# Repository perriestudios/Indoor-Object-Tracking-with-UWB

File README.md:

# <p align="center">Indoor-Object-Tracking-using-UWB </p>
## Introduction

<p align= "justify" > The objective of this project was to create an accurate general-purpose indoor localization system. Ultra-wideband(UWB) a wireless radio technology was chosen to achieve this. UWB offers high accuracy of localization, low latency, minimal interference and noise, and large bandwidth. DW1000 is an RF TX/RX IC manufactured by Decawave for UWB applications. This project uses the DW1000 IC in the form factor of module DWM1000. The hardware for the project was designed around this module with a few preferable features like access to the internet using an ESP8266-12E and programming support using the Arduino IDE. The system uses the Two-Way Ranging(TWR) technique for localization. The position computing is done by trilateration on the tag which is coupled with the object being tracked. A localization accuracy of about 12cm was achieved in a room of size 3x3m.</p>

## System Design

<p align= "justify" > In order to track an object, a device addressed "Tag" is attached to it. Devices callled "Anchors" are placed around the indoor environment to provide a spatial reference for the tag. Before the system starts tracking, the anchors should be fixed at different locations in the room and their coordinates are programmed in the tag. As shown in the above block diagram, the anchors are placed at (x1,y1),(x2,y2) and (x3,y3) respectively. Calibration of the DWM1000 is then done to accomodate for the slight difference in the radiation pattern of each antenna as mentioned in the datasheet of the module.</p>

## Working

<p align= "justify" > Once the setup is ready, the tag performs Two-Way Ranging to determine its distance from each anchor. The three distances are then substituted into the trilateration formula to determine the exact position. This data may then be shared with an anchor with a Wi-Fi module called the master anchor. The master anchor can then update the data anywhere over the internet. In this project, a dynamic webpage hosted on the ESP8266 displays the coordinates of the object. This entire cycle is repeated to track the position of the tag(in turn the object) in real time. A flow chart of the process is shown below:</p>

## Hardware
### PCB: Version 1

<p align= "justify" > As stated in the introduction, the hardware was designed around the DWM1000 module. Since the module operates between 2.8-3.6v, the system voltage was fixed to be 3v3. This also provided the convinience of using a handy single cell 750mah lipo battery. ATmega328P was chosen as the microcontroller due to my familiarity with it. An external 8MHz crystal oscillator was connected to ensure the microcontroller is clocked at the fastest possible speed at 3v3. The minimal circuit required for ESP8266 was designed and interfaced with the ATmega328P over the I2C bus while the DWM1000 uses SPI. IC MIC5219 a low cost 500mA LDO was used to regulate the supply voltage to 3v3 from the battery. Additionally, reverse polarity protection using a diode is added. Switches were provided to control power and reset of ATmega328P and ESP8266, while LED's were provided to indicate the status of power and DWM1000.</p>

<p align= "justify" > The above PCB was designed in Autodesk Eagle. The design files can be found in the folder Master_V1 under the Hardware section of this repository. </p>

### PCB: Version 2

<p align= "justify" > The major feature of version 2 addition of programming over the USB. In the previous version, the bootloader was initally burned using an ATMEL ICE debugger and the program written over UART using an Arduino Uno performing USB-TTL conversion. However, I found it very inconvienient to interconnect the Uno everytime, reset it during programming and reading the data serially. Hence, the popular USB-TTL converter CH340G was added to support quicker programming and access to serial monitor. Pads were placed on the bottom to burn the bootloader using pogo pins. I also reduced the size of the crystals and switches to achieve the smallest possible form factor. </p>

<p align= "justify" > The design files can be found under the Tag_V2 and Anchor_V2 folders respectively. The anchor design contains an additional ESP8266 placed in the bottom. </p>

### Enclosure

<p align= "justify" > An enclosure was designed to house the device in Autodesk Fusion 360. The base was intended to be 3d printed on a PLA base which the lid will be a transparent laser cut acrylic. The PCB will be screwed on to the enclosure. The design file can be found under the hardware section</p>

## Software

<p align= "justify" > The firmware for the project was completely written in Arduino IDE with <a href="https://github.com/thotro/arduino-dw1000" target="_blank" rel="noopener noreferrer">arduino-dw1000 library</a> developed by Thomas Trojer. The programs could be found under the software section of this repository. </p>

## Working

<p align= "justify" > After uploading the program, the tag should be set in calibration mode to perform TWR and correct the calibration constant. After this, open a browser and navigate to the IP addess mentioned in the serial monitor of the master-anchor. The position of the tag will be updated every 10s in real-time with an accuracy < 30cm.</p>

## Outcome

<p align= "justify" >This capstone project was undertaken as part of my UG curriculum. Version 2 of the hardware did not progress beyond the design stage due to my graduation in May 2020, during the middle of the pandemic here. Fortunately, I was able to demonstate the working of the system using the first version of the hardware to earn my degree. However, as a hobby project, I am working on a TDoA implementation of the system to be deployed at Beeclust MRSL for tracking robots. It will be replacement for the april tags currently used in the projects. There are certain aspects of the system that could still be improved. Feel free to contact me if you would like to improve this project.</p>

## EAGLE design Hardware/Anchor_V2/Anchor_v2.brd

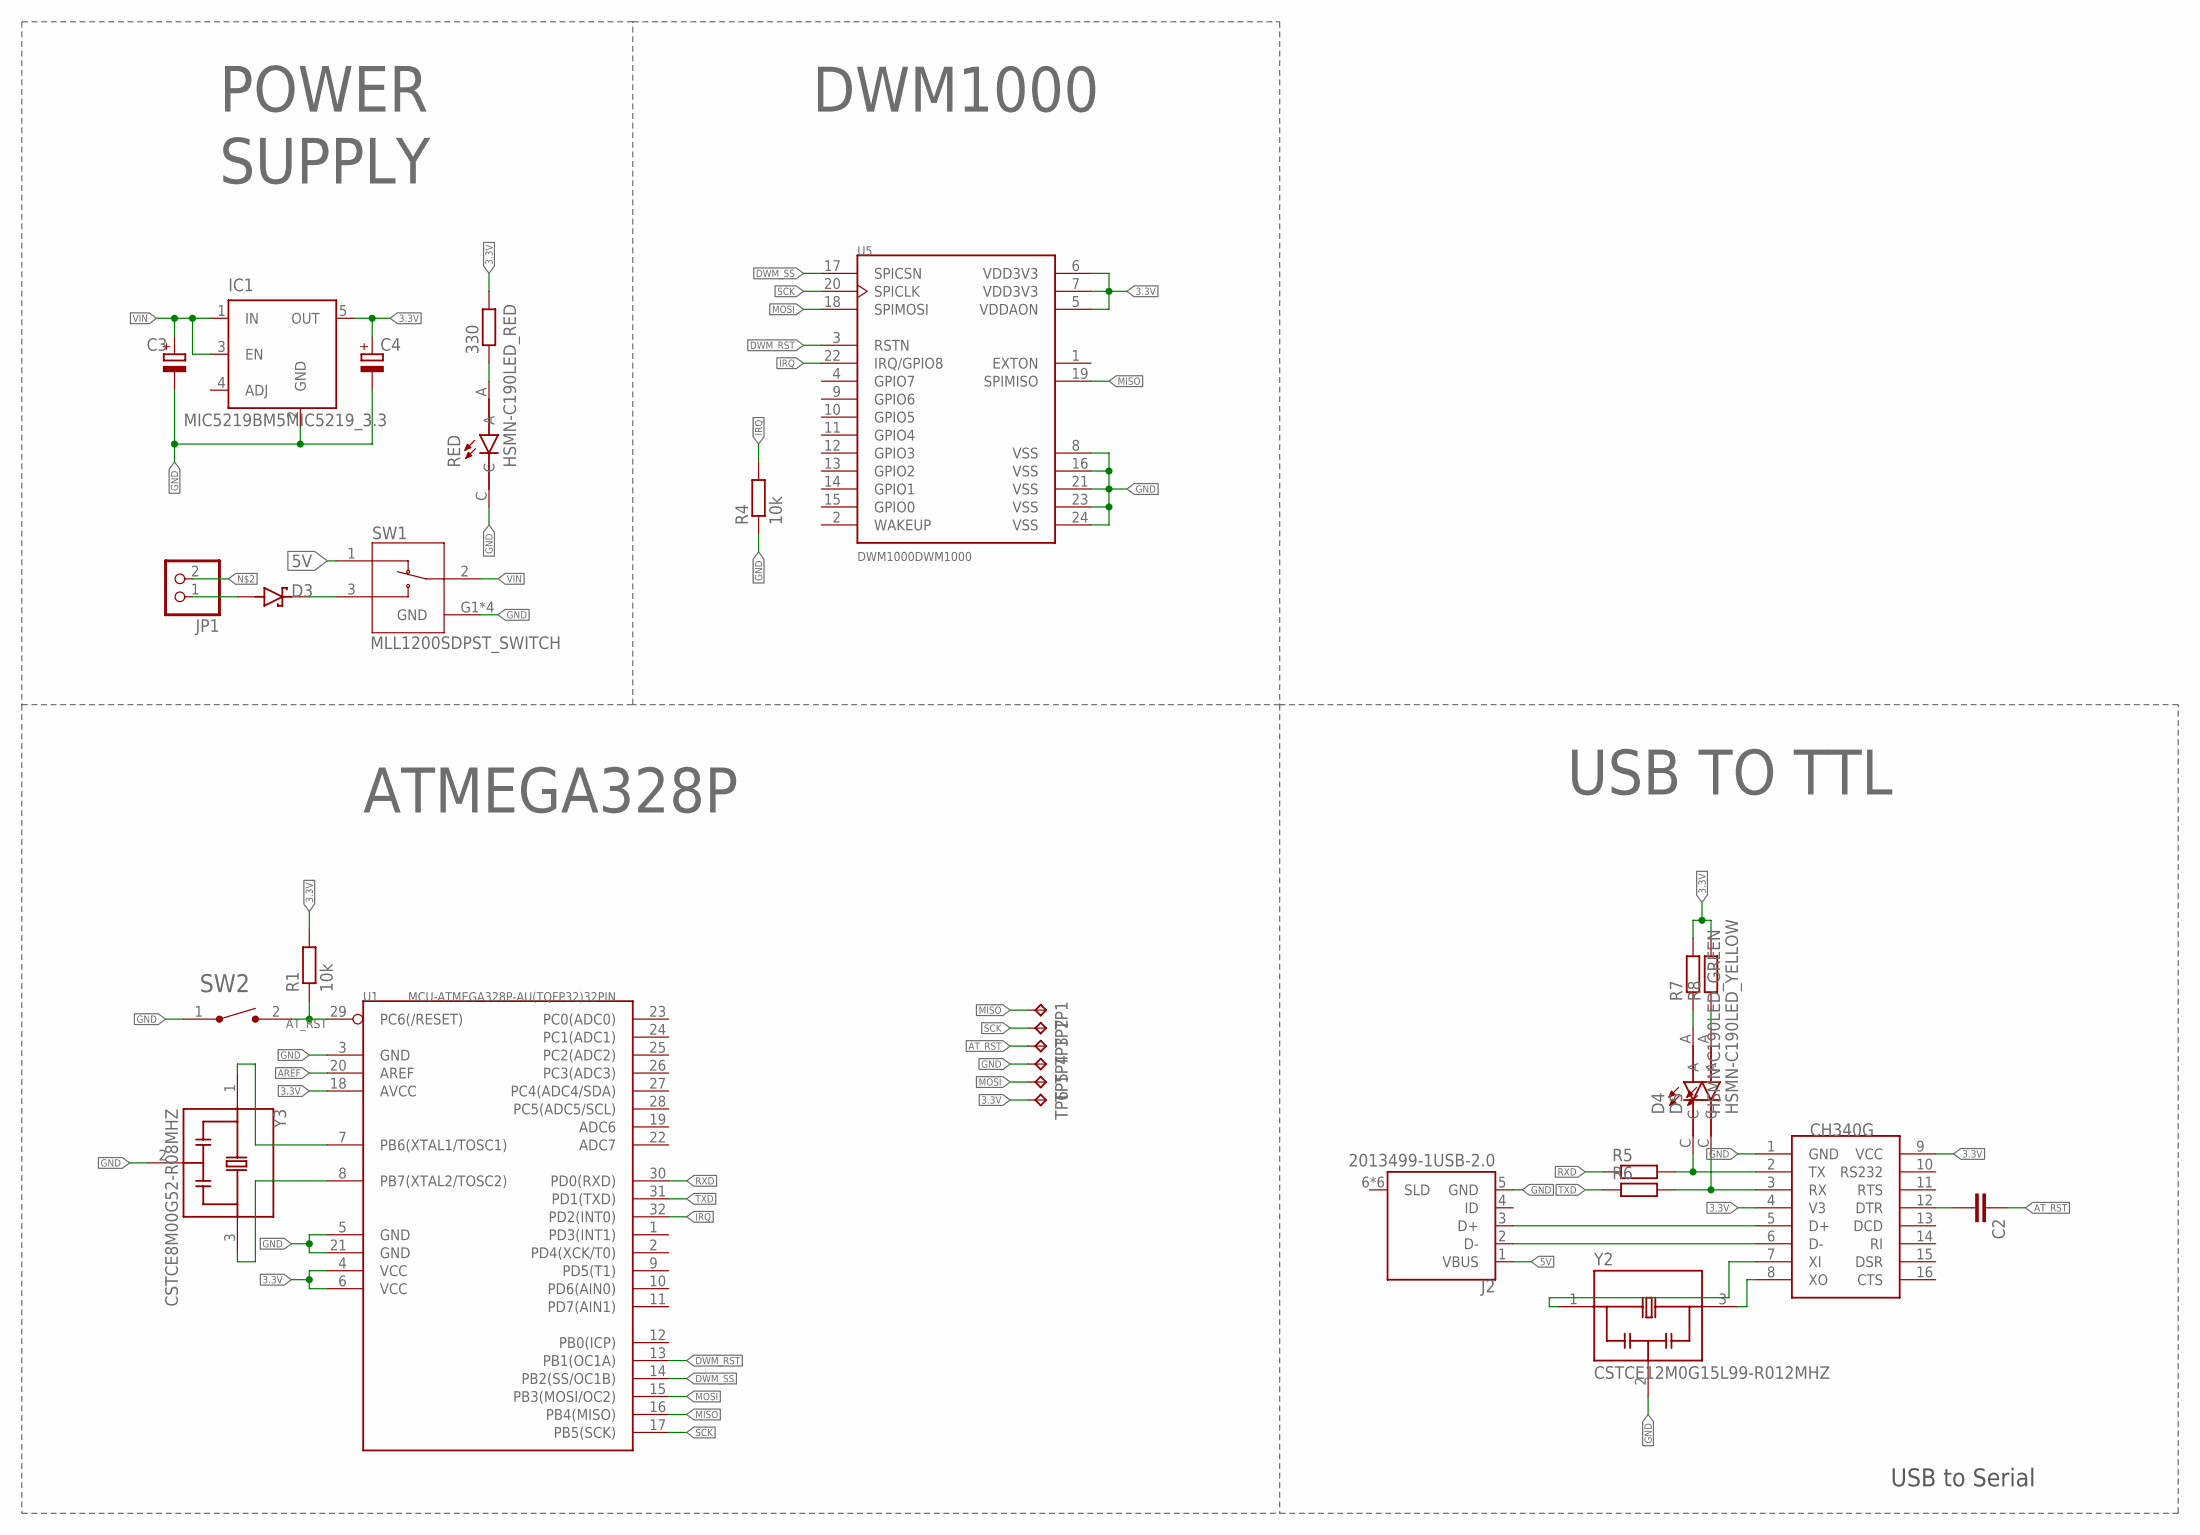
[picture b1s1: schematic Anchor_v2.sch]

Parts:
330: R-EU_R0603; R0603
C2: C-EUC0603; C0603
C3, C4: CPOL-EUA/3216-18R; A/3216-18R
D3: 1N5819HW-7-FSCHOTTKEYDIODE; SOD3715X145N_NEW
D4: HSMN-C190LED_GREEN; LEDM1608X80_NEW
D5: HSMN-C190LED_YELLOW; LEDM1608X80_NEW
IC1: MIC5219BM5MIC5219_3.3; SOT23-5_NEW
J2: 2013499-1USB-2.0; TE_2013499-1_NEW
JP1: PINHD-1X2; 1X02
R1, R4: 10k; R0603
R5, R6, R7, R8: R-EU_R0603; R0603
RED: HSMN-C190LED_RED; LEDM1608X80_NEW
SW1: MLL1200SDPST_SWITCH; SW_MLL1200S_NEW
SW2: FSMSMRESET_SPST; TE_FSMSM_NEW
TP1, TP2, TP3, TP4, TP5, TP6: TPB1,27; B1,27
U1: MCU-ATMEGA328P-AU(TQFP32)32PIN; TQFP32-0.8-7X7MM_NEW
U5: DWM1000DWM1000; XCVR_DWM1000_NEW
U$1: CH340G16PIN; SOIC16_NEW
Y2: CSTCE12M0G15L99-R012MHZ; OSC_CSTCE12M0G15L99-R0_NEW
Y3: CSTCE8M00G52-R08MHZ; OSC_CSTCE8M00G52-R0_NEW

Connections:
3.3V: 330.2, C4.+, IC1.5 (OUT), R1.2, R7.2, R8.2, TP6.TP, U1.4 (VCC), U1.6 (VCC), U1.18 (AVCC), U5.5 (VDDAON), U5.6 (VDD3V3), U5.7 (VDD3V3), U$1.4 (V3), U$1.9 (VCC)
5V: J2.1 (VBUS), SW1.1
AREF: U1.20 (AREF)
AT_RST: C2.1, R1.1, SW2.2, TP3.TP, U1.29 (PC6(/RESET))
DWM_RST: U1.13 (PB1(OC1A)), U5.3 (RSTN)
DWM_SS: U1.14 (PB2(SS/OC1B)), U5.17 (SPICSN)
GND: C3.-, C4.-, IC1.2 (GND), J2.5 (GND), R4.1, RED.C, SW1.G1 (GND), SW1.G2 (GND), SW1.G3 (GND), SW1.G4 (GND), SW2.1, TP4.TP, U1.3 (GND), U1.5 (GND), U1.21 (GND), U5.8 (VSS), U5.16 (VSS), U5.21 (VSS), U5.23 (VSS), U5.24 (VSS), U$1.1 (GND), Y2.2, Y3.2
IRQ: R4.2, U1.32 (PD2(INT0)), U5.22 (IRQ/GPIO8)
MISO: TP1.TP, U1.16 (PB4(MISO)), U5.19 (SPIMISO)
MOSI: TP5.TP, U1.15 (PB3(MOSI/OC2)), U5.18 (SPIMOSI)
unnamed: U1.7 (PB6(XTAL1/TOSC1)), Y3.1
unnamed: D3.A, JP1.1
unnamed: D3.C (K), SW1.3
unnamed: U1.8 (PB7(XTAL2/TOSC2)), Y3.3
unnamed: 330.1, RED.A
unnamed: D4.C, R5.2, U$1.2 (TX)
unnamed: C2.2, U$1.12 (DTR)
unnamed: U$1.8 (XO), Y2.3
unnamed: D5.C, R6.2, U$1.3 (RX)
unnamed: D4.A, R7.1
unnamed: D5.A, R8.1
unnamed: U$1.7 (XI), Y2.1
unnamed: J2.2 (D-), U$1.6 (D-)
unnamed: J2.3 (D+), U$1.5 (D+)
RXD: R5.1, U1.30 (PD0(RXD))
SCK: TP2.TP, U1.17 (PB5(SCK)), U5.20 (SPICLK)
TXD: R6.1, U1.31 (PD1(TXD))
VIN: C3.+, IC1.1 (IN), IC1.3 (EN), SW1.2

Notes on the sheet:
POWER
SUPPLY
USB to Serial
DWM1000
ATMEGA328P
USB TO TTL

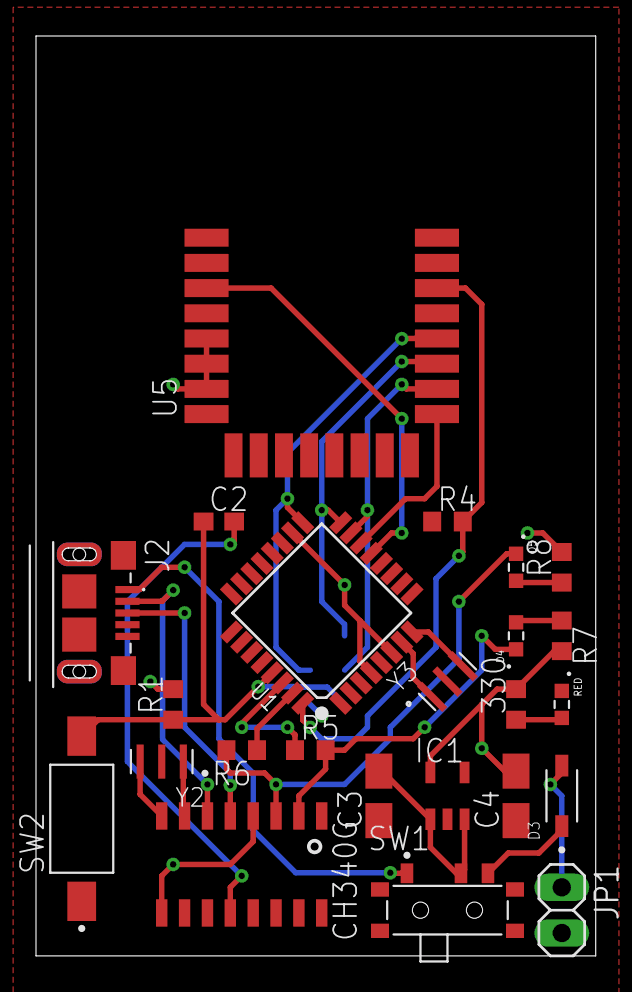
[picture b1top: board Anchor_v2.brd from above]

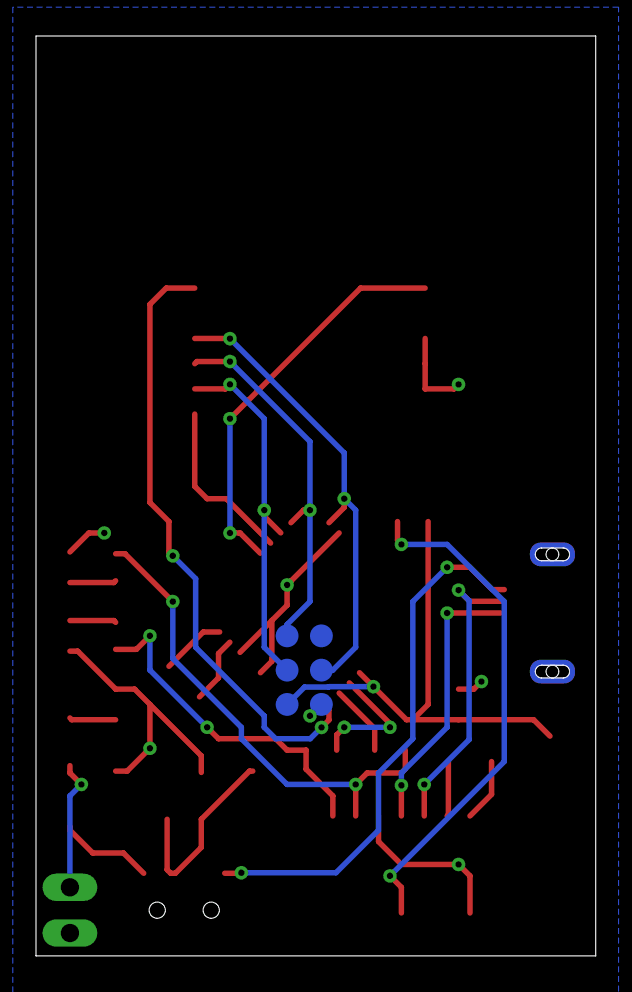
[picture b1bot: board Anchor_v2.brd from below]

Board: 2 copper layers, 31.1 x 51.1 mm, 30 parts (6 on the bottom side), 27 nets.

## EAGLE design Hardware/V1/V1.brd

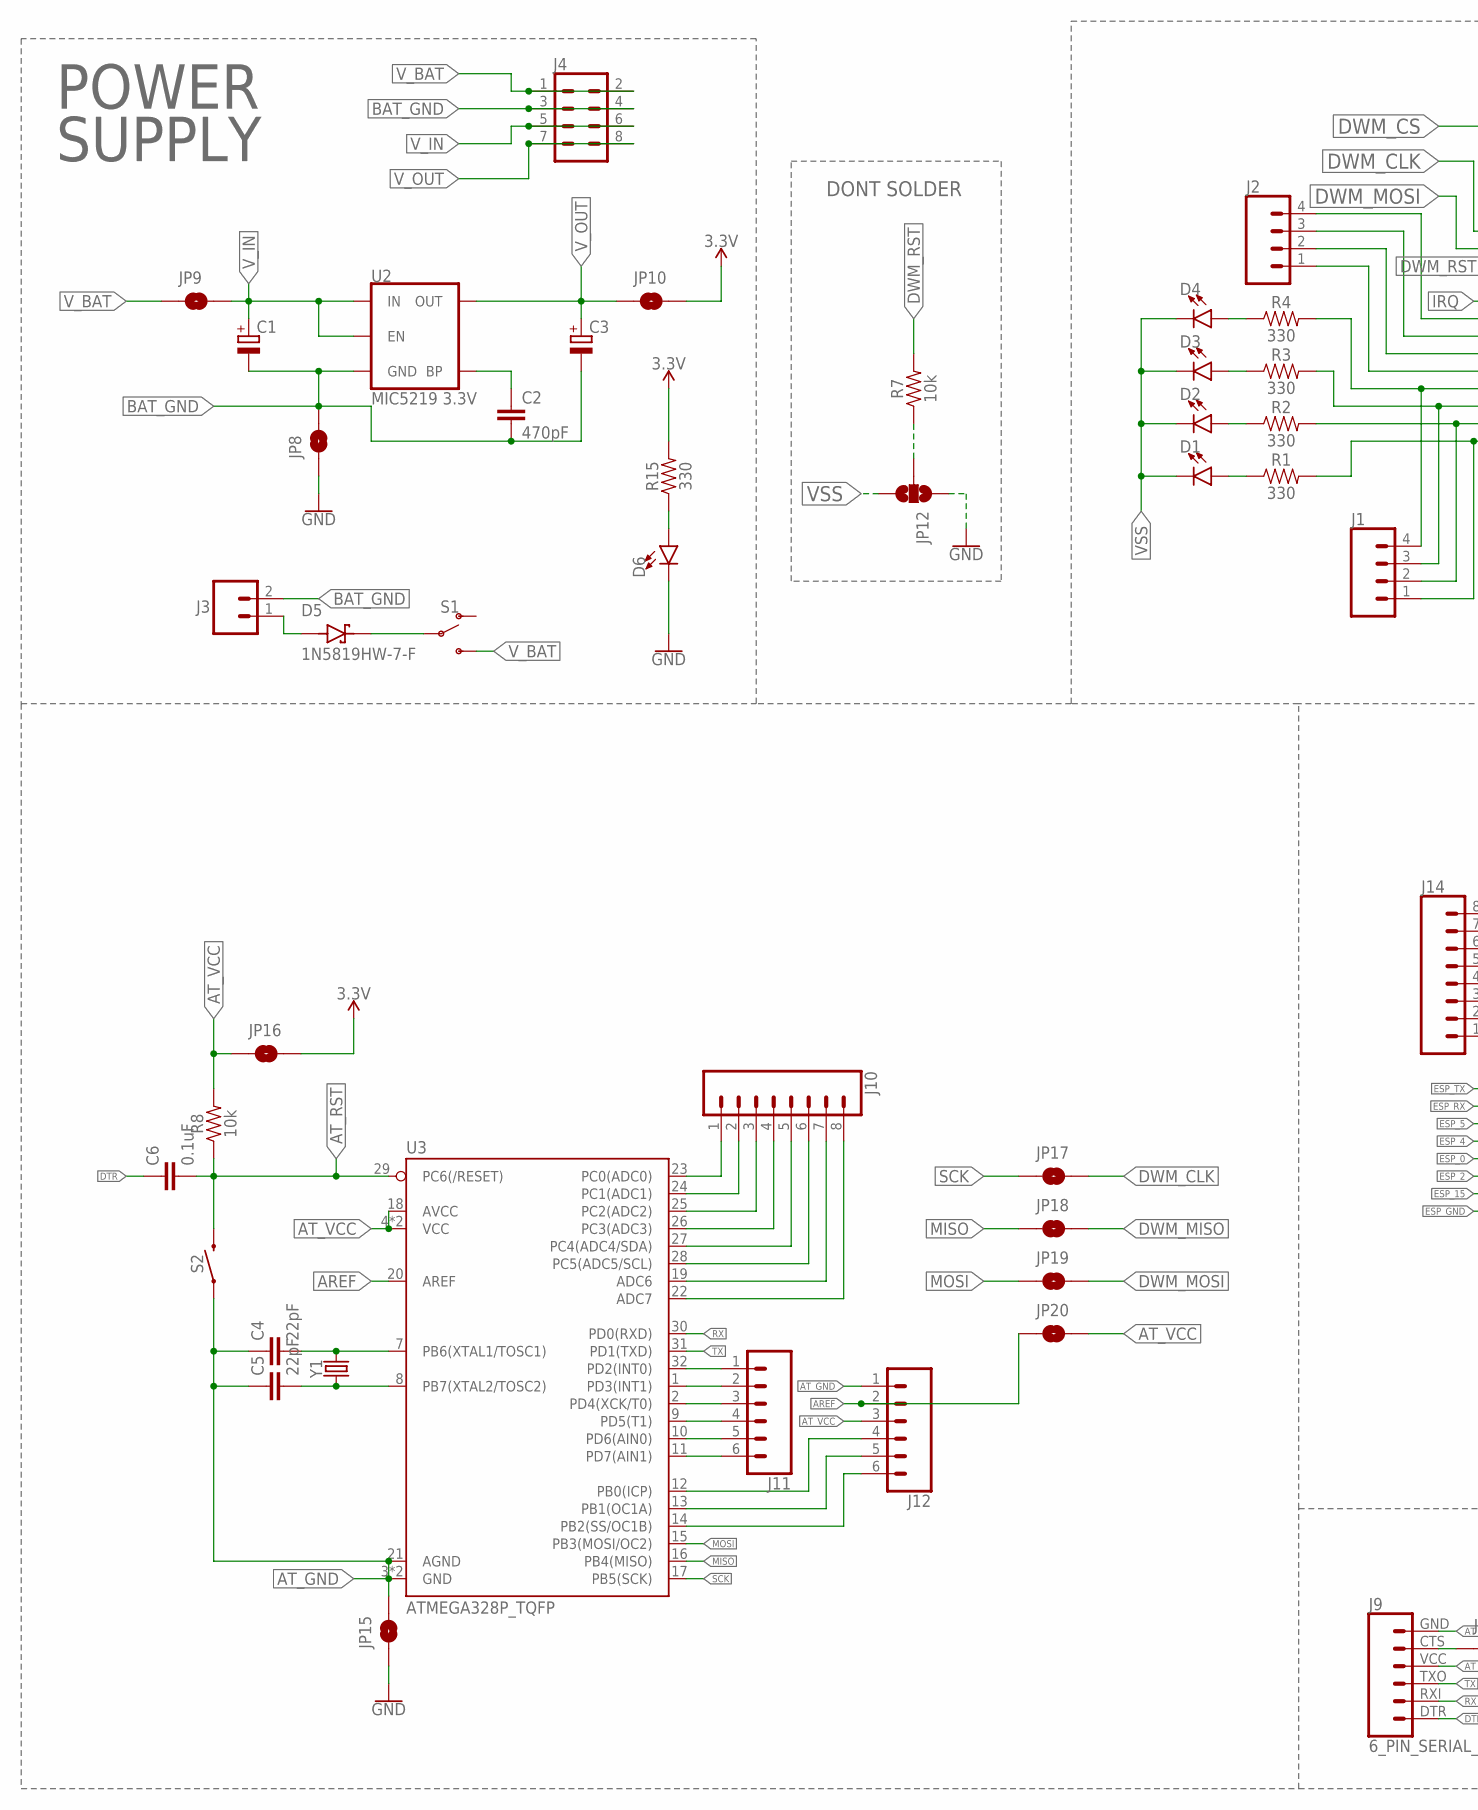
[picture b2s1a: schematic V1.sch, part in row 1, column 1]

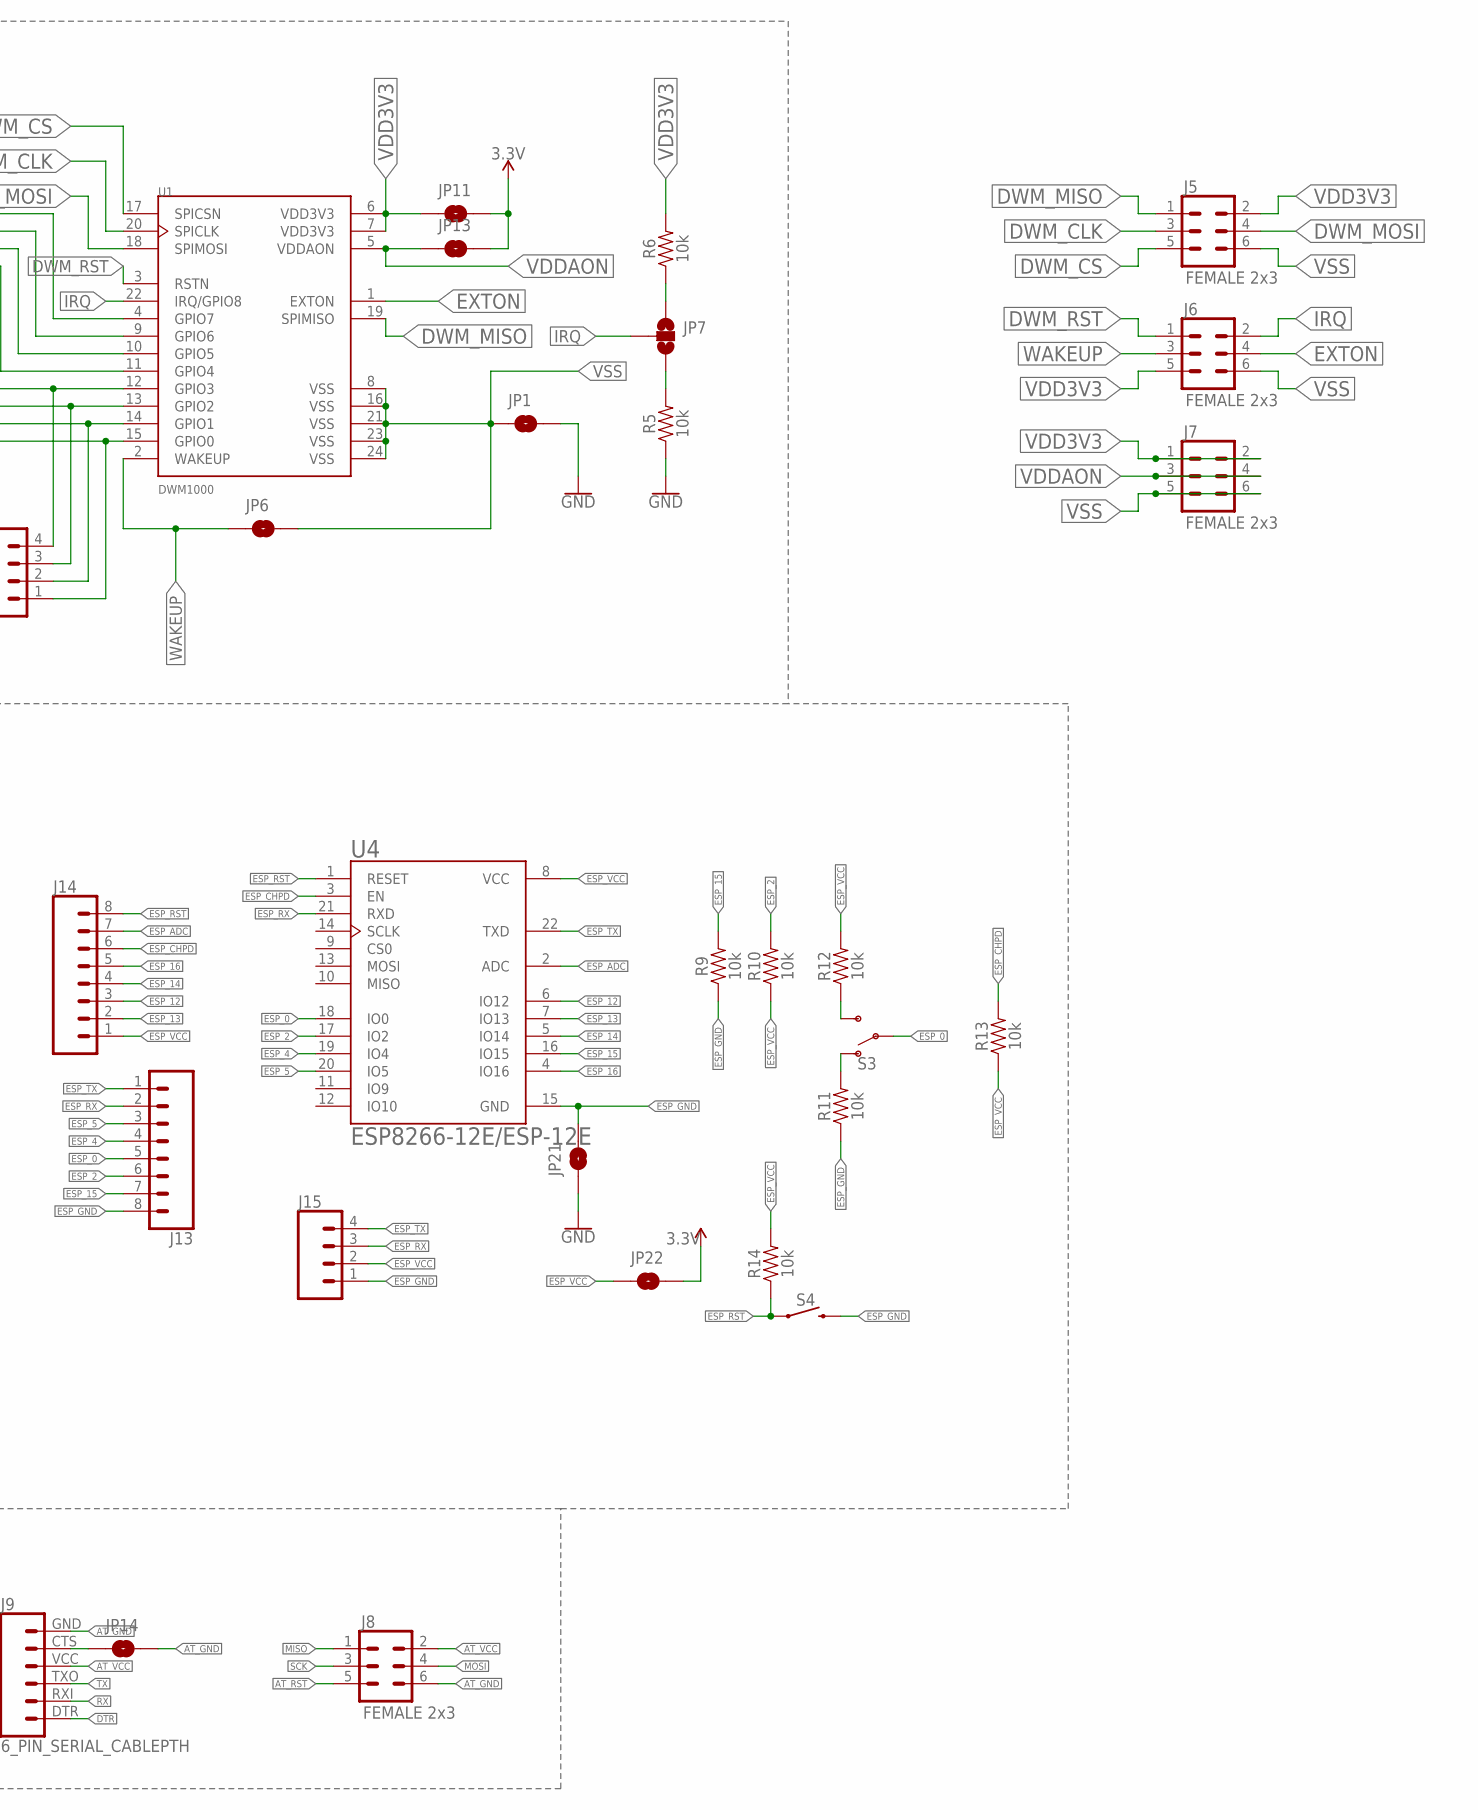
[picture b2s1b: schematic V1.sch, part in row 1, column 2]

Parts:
C1, C3: CPOL-EUSMCA; SMC_A
C2: 470pF; 0603
C4, C5: 22pF; 0603
C6: 0.1uF; 0603
D1, D2, D3, D4, D6: LED0603; LED-0603
D5: 1N5819HW-7-F; SOD3715X145N
J1, J2, J15: CONN_04; 1X04
J3: CONN_02; 1X02
J4: CONN_04X2; 2X4
J5, J6, J7, J8: FEMALE 2x3; 2X3
J9: 6_PIN_SERIAL_CABLEPTH; FTDI_BASIC
J10, J13, J14: CONN_08"; 1X08
J11, J12: CONN_06SILK_FEMALE_PTH; 1X06
JP1, JP6, JP8, JP9, JP10, JP11, JP13, JP14, JP15, JP16, JP17, JP18, JP19, JP20, JP21, JP22: JUMPER-SMT_2_NO_NO-SILK; SMT-JUMPER_2_NO_NO-SILK
JP7, JP12: JUMPER-SMT_3_NO_NO_SILK; SMT-JUMPER_3_0-NO_TRACE_NO-SILK
R1, R2, R3, R4, R15: 330; 0603
R5, R6, R7, R8, R9, R10, R11, R12, R13, R14: 10k; 0603
S1, S3: SWITCH-SPDT-SMD-AYZ0202; SWITCH_DPDT_SMD_AYZ0202
S2, S4: MOMENTARY-SWITCH-SPST-SMD-6.0X3.5MM; TACTILE_SWITCH_SMD_6.0X3.5MM
U1: DWM1000; XCVR_DWM1000
U2: MIC5219 3.3V; SOT23-5
U3: ATMEGA328P_TQFP; TQFP32-08
U4: ESP8266-12E/ESP-12E; XCVR_ESP8266-12E/ESP-12E
Y1: CRYSTALSMD-HC49UP; HC49UP

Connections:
3.3V: JP10.2, JP11.2, JP13.2, JP16.2, JP22.2, R15.2
AREF: J12.2, JP20.1, U3.20 (AREF)
AT_GND: C4.1, C5.1, J8.6, J9.GND (6), J12.1, JP14.2, JP15.2, S2.1, U3.3 (GND), U3.5 (GND), U3.21 (AGND)
AT_RST: C6.2, J8.5, R8.1, S2.2, U3.29 (PC6(/RESET))
AT_VCC: J8.2, J9.VCC (4), J12.3, JP16.1, JP20.2, R8.2, U3.4 (VCC), U3.6 (VCC), U3.18 (AVCC)
BAT_GND: C1.-, C2.2, C3.-, J3.2, J4.3, J4.4, JP8.2, U2.2 (GND)
DTR: C6.1, J9.DTR (1)
DWM_CLK: J5.3, JP17.2, U1.20 (SPICLK)
DWM_CS: J5.5, U1.17 (SPICSN)
DWM_MISO: J5.1, JP18.2, U1.19 (SPIMISO)
DWM_MOSI: J5.4, JP19.2, U1.18 (SPIMOSI)
DWM_RST: J6.1, R7.2, U1.3 (RSTN)
ESP_0: J13.5, S3.2, U4.18 (IO0)
ESP_2: J13.6, R10.2, U4.17 (IO2)
ESP_4: J13.4, U4.19 (IO4)
ESP_5: J13.3, U4.20 (IO5)
ESP_12: J14.3, U4.6 (IO12)
ESP_13: J14.2, U4.7 (IO13)
ESP_14: J14.4, U4.5 (IO14)
ESP_15: J13.7, R9.2, U4.16 (IO15)
ESP_16: J14.5, U4.4 (IO16)
ESP_ADC: J14.7, U4.2 (ADC)
ESP_CHPD: J14.6, R13.2, U4.3 (EN)
ESP_GND: J13.8, J15.1, JP21.2, R9.1, R11.1, S4.2, U4.15 (GND)
ESP_RST: J14.8, R14.1, S4.1, U4.1 (RESET)
ESP_RX: J13.2, J15.3, U4.21 (RXD)
ESP_TX: J13.1, J15.4, U4.22 (TXD)
ESP_VCC: J14.1, J15.2, JP22.1, R10.1, R12.2, R13.1, R14.2, U4.8 (VCC)
EXTON: J6.4, U1.1 (EXTON)
GND: D6.C, JP1.2, JP8.1, JP12.1, JP15.1, JP21.1, R5.1
IN_BAT: D5.C (K), S1.2
IRQ: J6.2, JP7.2, U1.22 (IRQ/GPIO8)
MISO: J8.1, JP18.1, U3.16 (PB4(MISO))
MOSI: J8.4, JP19.1, U3.15 (PB3(MOSI/OC2))
unnamed: J1.4, R4.2, U1.12 (GPIO3)
unnamed: C2.1, U2.4 (BP)
unnamed: J1.3, R3.2, U1.13 (GPIO2)
unnamed: J1.2, R2.2, U1.14 (GPIO1)
unnamed: J1.1, R1.2, U1.15 (GPIO0)
unnamed: D4.A, R4.1
unnamed: D3.A, R3.1
unnamed: D2.A, R2.1
unnamed: D1.A, R1.1
unnamed: J2.1, U1.11 (GPIO4)
unnamed: JP7.1, R6.1
unnamed: J2.2, U1.10 (GPIO5)
unnamed: J2.3, U1.9 (GPIO6)
unnamed: J2.4, U1.4 (GPIO7)
unnamed: JP7.3, R5.2
unnamed: D5.A, J3.1
unnamed: C4.2, U3.7 (PB6(XTAL1/TOSC1)), Y1.2
unnamed: JP12.2, R7.1
unnamed: C5.2, U3.8 (PB7(XTAL2/TOSC2)), Y1.1
unnamed: J10.1, U3.23 (PC0(ADC0))
unnamed: J10.2, U3.24 (PC1(ADC1))
unnamed: J10.3, U3.25 (PC2(ADC2))
unnamed: J10.4, U3.26 (PC3(ADC3))
unnamed: J9.CTS (5), JP14.1
unnamed: J10.5, U3.27 (PC4(ADC4/SDA))
unnamed: J10.6, U3.28 (PC5(ADC5/SCL))
unnamed: J10.7, U3.19 (ADC6)
unnamed: J10.8, U3.22 (ADC7)
unnamed: J11.1, U3.32 (PD2(INT0))
unnamed: J11.2, U3.1 (PD3(INT1))
unnamed: J11.3, U3.2 (PD4(XCK/T0))
unnamed: J11.4, U3.9 (PD5(T1))
unnamed: J11.5, U3.10 (PD6(AIN0))
unnamed: J11.6, U3.11 (PD7(AIN1))
unnamed: J12.5, U3.13 (PB1(OC1A))
unnamed: J12.4, U3.12 (PB0(ICP))
unnamed: J12.6, U3.14 (PB2(SS/OC1B))
unnamed: R11.2, S3.1 (O)
unnamed: R12.1, S3.3 (S)
unnamed: D6.A, R15.1
RX: J9.RXI (2), U3.30 (PD0(RXD))
SCK: J8.3, JP17.1, U3.17 (PB5(SCK))
TX: J9.TXO (3), U3.31 (PD1(TXD))
VDD3V3: J5.2, J6.5, J7.1, J7.2, JP11.1, R6.2, U1.6 (VDD3V3), U1.7 (VDD3V3)
VDDAON: J7.3, J7.4, JP13.1, U1.5 (VDDAON)
VSS: D1.C, D2.C, D3.C, D4.C, J5.6, J6.6, J7.5, J7.6, JP1.1, JP6.2, JP12.3, U1.8 (VSS), U1.16 (VSS), U1.21 (VSS), U1.23 (VSS), U1.24 (VSS)
V_BAT: J4.1, J4.2, JP9.1, S1.3 (S)
V_IN: C1.+, J4.5, J4.6, JP9.2, U2.1 (IN), U2.3 (EN)
V_OUT: C3.+, J4.7, J4.8, JP10.1, U2.5 (OUT)
WAKEUP: J6.3, JP6.1, U1.2 (WAKEUP)

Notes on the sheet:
POWER
SUPPLY
DONT SOLDER

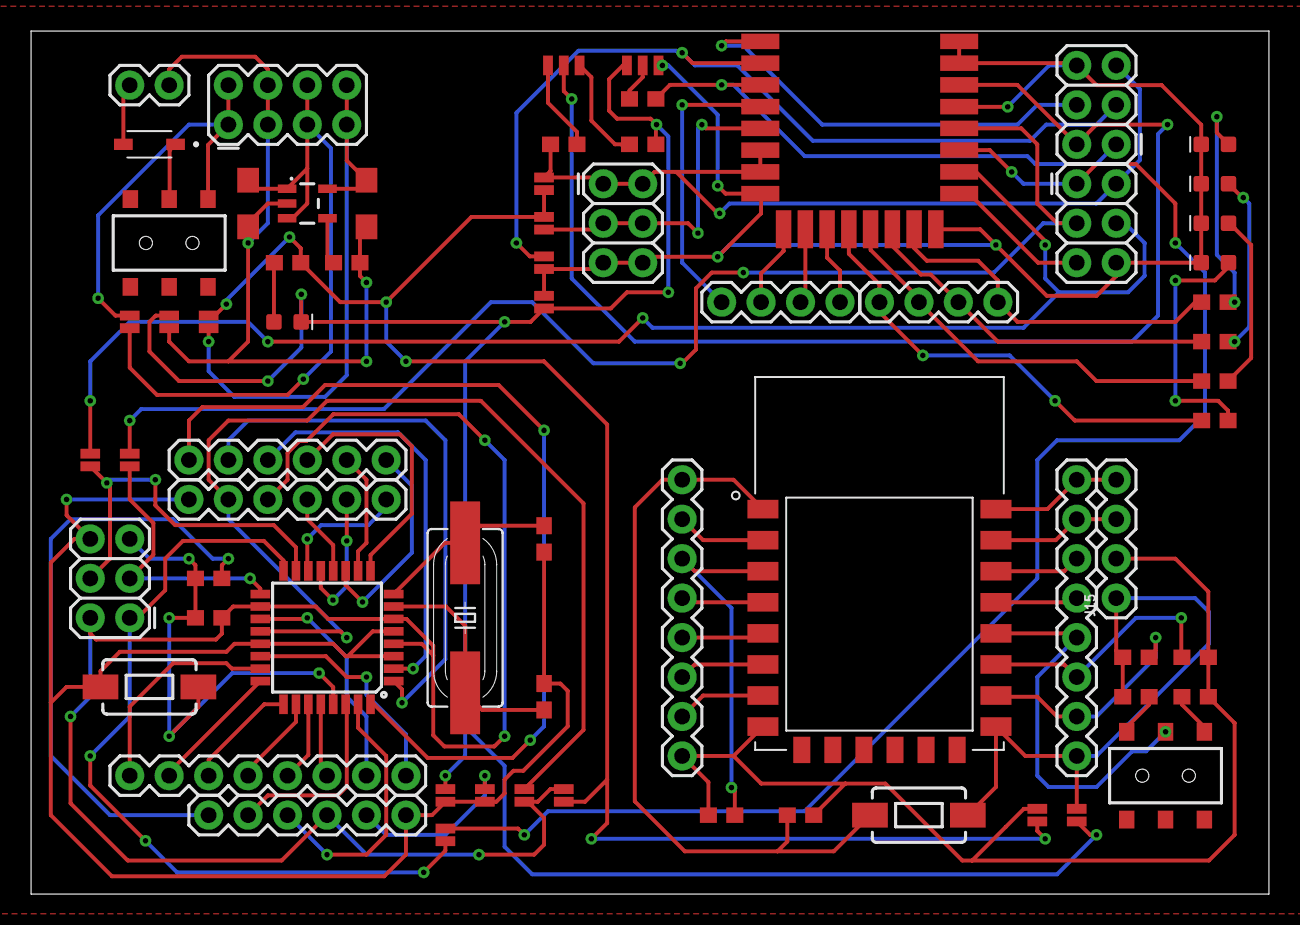
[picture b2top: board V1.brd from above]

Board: 2 copper layers, 79.7 x 55.5 mm, 69 parts (0 on the bottom side), 84 nets.

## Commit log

2020-05-11 Set theme jekyll-theme-slate
2020-12-01 Initial Push
2021-03-15 Sorted Name Discrepancy
2021-03-15 Added Fusion360 Mechanical Design
2021-03-15 Corrected name discrepancy in Software

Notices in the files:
parts and their libraries:
SparkFun-Capacitors: Licensing: Creative Commons ShareAlike 4.0 International - https://creativecommons.org/licenses/by-sa/4.0
